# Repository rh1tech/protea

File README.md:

# Protea

Protea is a custom development board designed in KiCad that bridges the gap between vintage computing and modern connectivity. Named after the protea flower, which itself derives from Proteus, son of Poseidon in Greek mythology, this board embodies the shape-shifting adaptability that made the mythological Proteus legendary. Just as the protea flower has survived and adapted for over 300 million years, becoming a symbol of longevity and endurance, the Protea development board is designed to endure and adapt across different technological eras.

The protea’s incredible diversity of forms - which inspired Carl Linnaeus to name it after the shape-shifting Proteus - mirrors this board’s versatility in connecting vintage computing with modern internet capabilities.

Documentation: [rh1.tech](https://rh1.tech/projects/protea)

## Hardware Specifications

### Primary Controller:

- RP2040 Microcontroller - directly soldered on board
- Dual-core ARM Cortex-M0+ processor running up to 133 MHz
- 264kB on-chip SRAM for program execution
- 8 Programmable I/O (PIO) state machines for custom peripheral support

### Connectivity Controller:
- ESP8266 Microcontroller - integrated Wi-Fi-to-Serial modem functionality
- 802.11 Wi-Fi support for internet connectivity
- AT command compatibility for seamless vintage computer integration

### Interface Ports:

- USB Port - keyboard input support with hub compatibility
- DB9 Serial Port - RS232 connectivity for vintage computers and external devices
- HDMI Port - native digital video output without conversion
- Power Input - USB-powered operation

## Firmware Ecosystem

Protea operates using two complementary firmware components:

### [Iris](https://github.com/rh1tech/iris) Terminal Software

- VT100/VT102 terminal emulation with full attribute support
- Instant-on operation with no boot time
- Configurable fonts and display settings
- PETSCII mode for Commodore compatibility

### [Hermes](https://github.com/rh1tech/hermes) Wi-Fi Modem

- Hayes-compatible AT command set
- Telnet protocol support for internet connectivity
- Transparent Wi-Fi-to-Serial bridge operation
- BBS and vintage online service access

## Use Cases

Protea enables seamless connection of classic computers to modern internet resources, providing access to text-mode BBS systems and online communities that maintain the spirit of early computing culture. The board serves as a bridge between RS232 devices and Wi-Fi networks, ensuring that vintage computing enthusiasts can maintain an authentic retro computing experience while leveraging contemporary internet connectivity.

The platform supports text-mode internet browsing for those who prefer minimalist computing approaches, while also serving as a foundation for terminal-based development environments. Protea is particularly well-suited for retrocomputing projects that require modern connectivity solutions, and functions as an educational platform for understanding the fundamentals of serial communications and terminal operations.

## Design Philosophy

Like the protea flower that has endured and adapted for over 300 million years, and the shape-shifting Proteus of Greek mythology, this development board embodies longevity, adaptability, and transformation. The board’s dual-microcontroller architecture ensures optimal performance for both local terminal processing and network communications, demonstrating the same versatility that characterizes its mythological and botanical namesakes.

The custom PCB design prioritizes signal integrity and reliable connectivity, making it suitable for both hobbyist projects and professional applications requiring robust serial terminal functionality.

## Getting Started

1.	Flash Firmware - Load [Iris](https://github.com/rh1tech/iris) onto the RP2040 and [Hermes](https://github.com/rh1tech/hermes) onto the ESP8266
2.	Connect Display - Attach HDMI monitor for terminal output
3.	Add Keyboard - Connect USB keyboard for input
4.	Configure Wi-Fi - Set up wireless connectivity through Hermes
5.	Connect Devices - Use DB9 port for vintage computer or RS232 device connections

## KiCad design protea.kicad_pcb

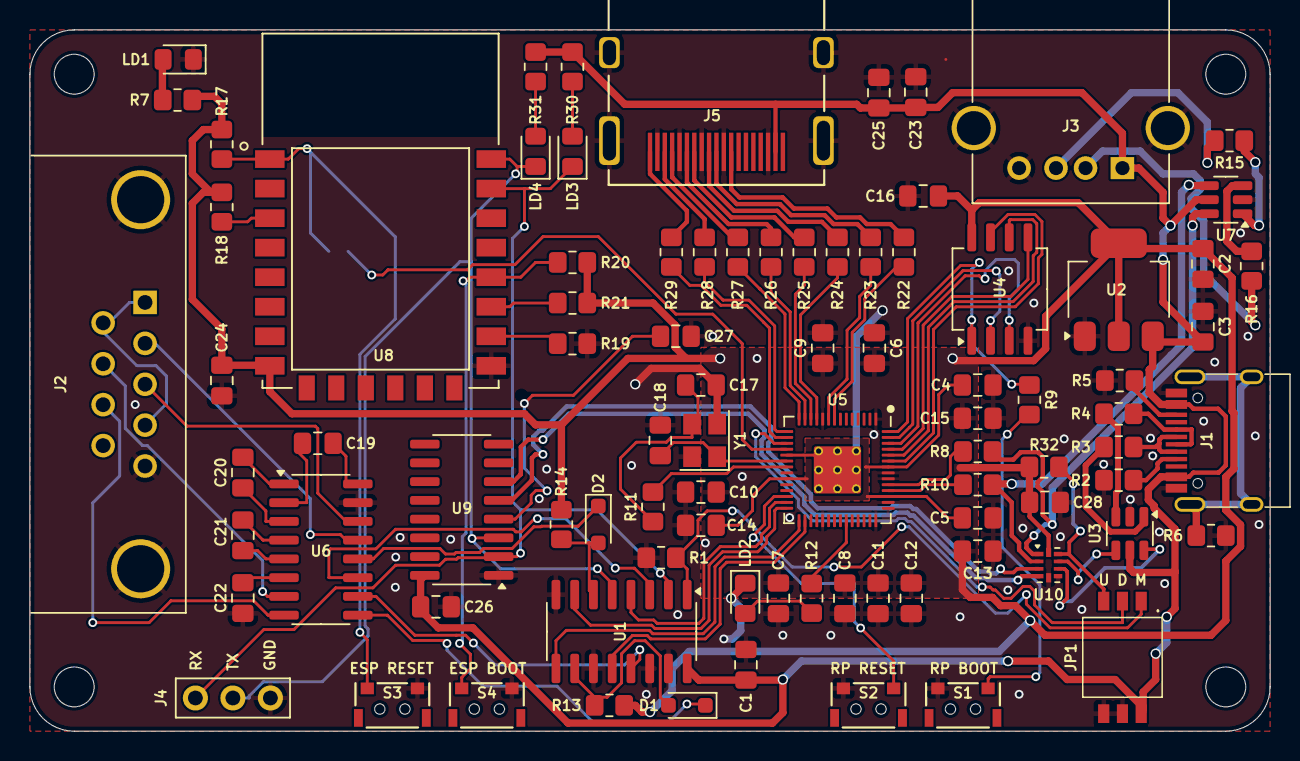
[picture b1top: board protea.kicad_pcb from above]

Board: 2 copper layers, 84.0 x 47.5 mm, 92 parts (1 on the bottom side), 89 nets.

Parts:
C1, C4, C5, C6, C7, C8, C9, C10, C11, C12, C13, C16, C25, C26, C27, C28: 100n; Capacitor (0805)
C2, C3, C23: 10u; Capacitor (0805)
C14, C15, C19, C20, C21, C22, C24: 1u; Capacitor (0805)
C17, C18: 15p; Capacitor (0805)
D1, D2: 1N4148; Diode (SOD-323)
H1, H2, H3, H4: MountingHole; Mounting Hole (2.7mm)
J1: USB4215-03-A; USB Type C
J2: D-SUB 9 Male; D-SUB (9 pin, male, top mount)
J3: 676430910; USB Type A (single)
J4: ESP8266 Prog; Pin Header (1x03)
J5: HDMI Female; HDMI (female)
JP1: DS05-127-2-03BK-SMT-TR; DS05127203BKSMTTR
JP2: ESP Reset; Jumper (solder)
LD1: Green; LED (0805)
LD2: Blue; LED (0805)
LD3, LD4: Orange; LED (0805)
R1, R17, R18, R19, R20, R21, R32: 10K; Resistor (0805)
R2, R5: 5.1K; Resistor (0805)
R3, R4, R15, R16: 22R; Resistor (0805)
R6: 1M; Resistor (0805)
R7, R9, R11, R12, R13, R14: 1K; Resistor (0805)
R8, R10: 27R; Resistor (0805)
R22, R23, R24, R25, R26, R27, R28, R29: 270R; Resistor (0805)
R30, R31: 1.5K; Resistor (0805)
S1: Boot; TACT-SIDE-4623
S2, S3: Reset; TACT-SIDE-4623
S4: Flash; TACT-SIDE-4623
U1: SN74CBT3257CDR; SOP-16
U2: NCP1117 3.3; SOT-223
U3, U7: USBLC6-2SC6; SOT-23-6
U4: W25Q128JVSIQ; SOIC-8
U5: RP2040; QFN 56
U6: MAX232CSE+; SOP-16
U8: ESP8266 ESP-12F; ESP8266 ESP-12E
U9: CH340C; SOP-16
U10: TS3USB221RSER; UQFN-10
Y1: 12 MHz Passive; Crystal (3225)

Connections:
+3V3: C2.1, C6.1, C7.1, C8.1, C9.1, C10.1, C11.1, C12.1, C13.1, C15.1, C16.1, C24.1, C28.2, R7.2, R13.2, R14.2, R17.1, R18.1, R20.1, R21.1, R32.1, U2.2 (VO), U4.8 (VCC), U5.1 (IOVDD), U5.10 (IOVDD), U5.22 (IOVDD), U5.33 (IOVDD), U5.42 (IOVDD), U5.43 (ADC_AVDD), U5.44 (VREG_IN), U5.48 (USB_VDD), U5.49 (IOVDD), U8.8 (VCC), U10.10 (VCC)
/ESP_RESET: JP2.2 (B), R17.2, S3.2, U8.1 (RESET)
/ESP_RXD: J4.1, LD3.1 (K), U1.2 (1B1), U8.21 (RXD), U9.2 (TxD)
/ESP_TXD: J4.2, LD4.1 (K), U1.5 (2B1), U8.22 (TXD), U9.3 (RxD)
/GPIO6: R22.2, U5.8 (GPIO6)
/GPIO7: R23.2, U5.9 (GPIO7)
/GPIO8: R24.2, U5.11 (GPIO8)
/GPIO9: R25.2, U5.12 (GPIO9)
/GPIO10: R26.2, U5.13 (GPIO10)
/GPIO11: R27.2, U5.14 (GPIO11)
/GPIO12: R28.2, U5.15 (GPIO12)
/GPIO13: R29.2, U5.16 (GPIO13)
/GPIO14: JP1.2, U5.17 (GPIO14)
/GPIO15: JP2.1 (A), U5.18 (GPIO15)
/GPIO16: U1.4 (1A), U5.27 (GPIO16)
/GPIO17: U1.7 (2A), U5.28 (GPIO17)
/GPIO18: U1.9 (3A), U5.29 (GPIO18)
/GPIO19: U1.12 (4A), U5.30 (GPIO19)
/PW_D+: U3.4 (I/O2), U10.8 (D+)
/PW_D-: U3.6 (I/O1), U10.7 (D-)
/RP2040/GPIO25: R12.2, U5.37 (GPIO25)
/RP2040/QSPI_SCLK: U4.6 (CLK), U5.52 (QSPI_SCLK)
/RP2040/QSPI_SD0: U4.5 (DI(IO0)), U5.53 (QSPI_SD0)
/RP2040/QSPI_SD1: U4.2 (DO(IO1)), U5.55 (QSPI_SD1)
/RP2040/QSPI_SD2: U4.3 (IO2), U5.54 (QSPI_SD2)
/RP2040/QSPI_SD3: U4.7 (IO3), U5.51 (QSPI_SD3)
/RP2040/QSPI_SS: R9.1, U4.1 (~CS), U5.56 (QSPI_SS)
/RP2040/XIN: C18.1, U5.20 (XIN), Y1.1
/RP2040/XOUT: R11.1, U5.21 (XOUT)
/RP_D+: R8.1, U7.6 (I/O1), U10.1 (1D+)
/RP_D-: R10.1, U7.4 (I/O2), U10.2 (1D-)
/RS232/C1+: C20.2, U6.1 (C1+)
/RS232/C1-: C20.1, U6.3 (C1-)
/RS232/C2+: C21.2, U6.4 (C2+)
/RS232/C2-: C21.1, U6.5 (C2-)
/RS232/CTS_IN: J2.7, U6.7 (T2OUT)
/RS232/CTS_MAX: D1.1 (K), U6.9 (R2OUT)
/RS232/RTS_IN: J2.8, U6.8 (R2IN)
/RS232/RX_IN: J2.3, U6.14 (T1OUT)
/RS232/RX_MAX: D2.1 (K), U6.12 (R1OUT)
/RS232/TX_IN: J2.2, U6.13 (R1IN)
/RS232/V+: C19.1, U6.2 (V+)
/RS232/V-: C22.1, U6.6 (V-)
/RS232_CTS: D1.2 (A), R13.1, U1.10 (3B2)
/RS232_RTS: U1.13 (4B2), U6.10 (T2IN)
/RS232_RX: D2.2 (A), R14.1, U1.6 (2B2)
/RS232_TX: U1.3 (1B2), U6.11 (T1IN)
/RS232_VBUS: C19.2, U6.16 (VCC)
/RUN: S2.1, U5.26 (RUN)
/SN74_S: JP1.1, R1.2, U1.1 (S)
/USBMPXSW: JP1.3, R32.2, U10.9 (S)
/UT_D+: U9.5 (D+), U10.3 (2D+)
/UT_D-: U9.6 (D-), U10.4 (2D-)
GND: C1.1, C2.2, C3.2, C4.2, C5.2, C6.2, C7.2, C8.2, C9.2, C10.2, C11.2, C12.2, C13.2, C14.2, C15.2, C16.2, C17.2, C18.2, C22.2, C23.1, C24.2, C25.2, C26.2, C27.2, C28.1, J1.1 (GND), J1.12 (GND), J2.5, J3.4 (GND), J3.5 (Shield), J4.3, J5.2 (G_D2), J5.5 (G_D1), J5.8 (G_D0), J5.11 (G_CLK), J5.17 (G_DDC/CEC), J5.20 (SHIELD1), J5.21 (SHIELD2), J5.22 (SHIELD3), J5.23 (SHIELD4), JP1.4, JP1.5, LD1.1 (K), LD2.1 (K), R1.1, R2.1, R5.1, R6.2, R19.1, S1.2, S2.2, S3.1, S4.1, U1.8 (GND), U1.11 (3B1), U1.14 (4B1), U1.15 (~OE), U2.1 (GND), U3.2 (GND), U4.4 (GND), U5.19 (TESTEN), U5.57 (GND), U6.15 (GND), U7.2 (GND), U8.15 (GND), U9.1 (GND), U10.5 (GND), U10.6 (~OE), Y1.2, Y1.4
unnamed: C17.1, R11.2, Y1.3
unnamed: J1.4 (CC1), R2.2
unnamed: J1.10 (CC2), R5.2
unnamed: J1.5 (DN2), J1.7 (DN1), R3.2
unnamed: J1.6 (DP1), J1.8 (DP2), R4.2
unnamed: J1.13 (SHIELD), R6.1
unnamed: J2.1, J2.4, J2.6
unnamed: J3.3 (D+), R15.2
unnamed: J3.2 (D-), R16.2
unnamed: J5.12 (CLKN), R22.1
unnamed: J5.10 (CLKP), R23.1
unnamed: J5.9 (D0N), R24.1
unnamed: J5.7 (D0P), R25.1
unnamed: J5.6 (D1N), R26.1
unnamed: J5.4 (D1P), R27.1
unnamed: J5.3 (D2N), R28.1
unnamed: J5.1 (D2P), R29.1
unnamed: LD1.2 (A), R7.1
unnamed: LD2.2 (A), R12.1
unnamed: LD3.2 (A), R30.1
unnamed: LD4.2 (A), R31.2
unnamed: R3.1, U3.1 (I/O1)
unnamed: R4.1, U3.3 (I/O2)
unnamed: R9.2, S1.1
unnamed: R15.1, U7.1 (I/O1)
unnamed: R16.1, U7.3 (I/O2)
unnamed: R10.2, U5.46 (USB_DM)
unnamed: R8.2, U5.47 (USB_DP)
unnamed: C4.1, C5.1, C14.1, U5.23 (DVDD), U5.45 (VREG_VOUT), U5.50 (DVDD)
unnamed: R18.2, U8.3 (EN)
unnamed: R20.2, S4.2, U8.18 (IO0)
unnamed: R21.2, U8.17 (IO2)
unnamed: R19.2, U8.16 (IO15)
unnamed: C27.1, U9.4 (3V)
VBUS: C1.2, C3.1, C23.2, C25.1, C26.1, J1.2 (VBUS), J1.11 (VBUS), J3.1 (VBUS), J5.18 (+5V), JP1.6, R30.2, R31.1, U1.16 (VCC), U2.3 (VI), U3.5 (VBUS), U7.5 (VBUS), U9.16 (VCC)

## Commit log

2025-06-26 Added license & readme
